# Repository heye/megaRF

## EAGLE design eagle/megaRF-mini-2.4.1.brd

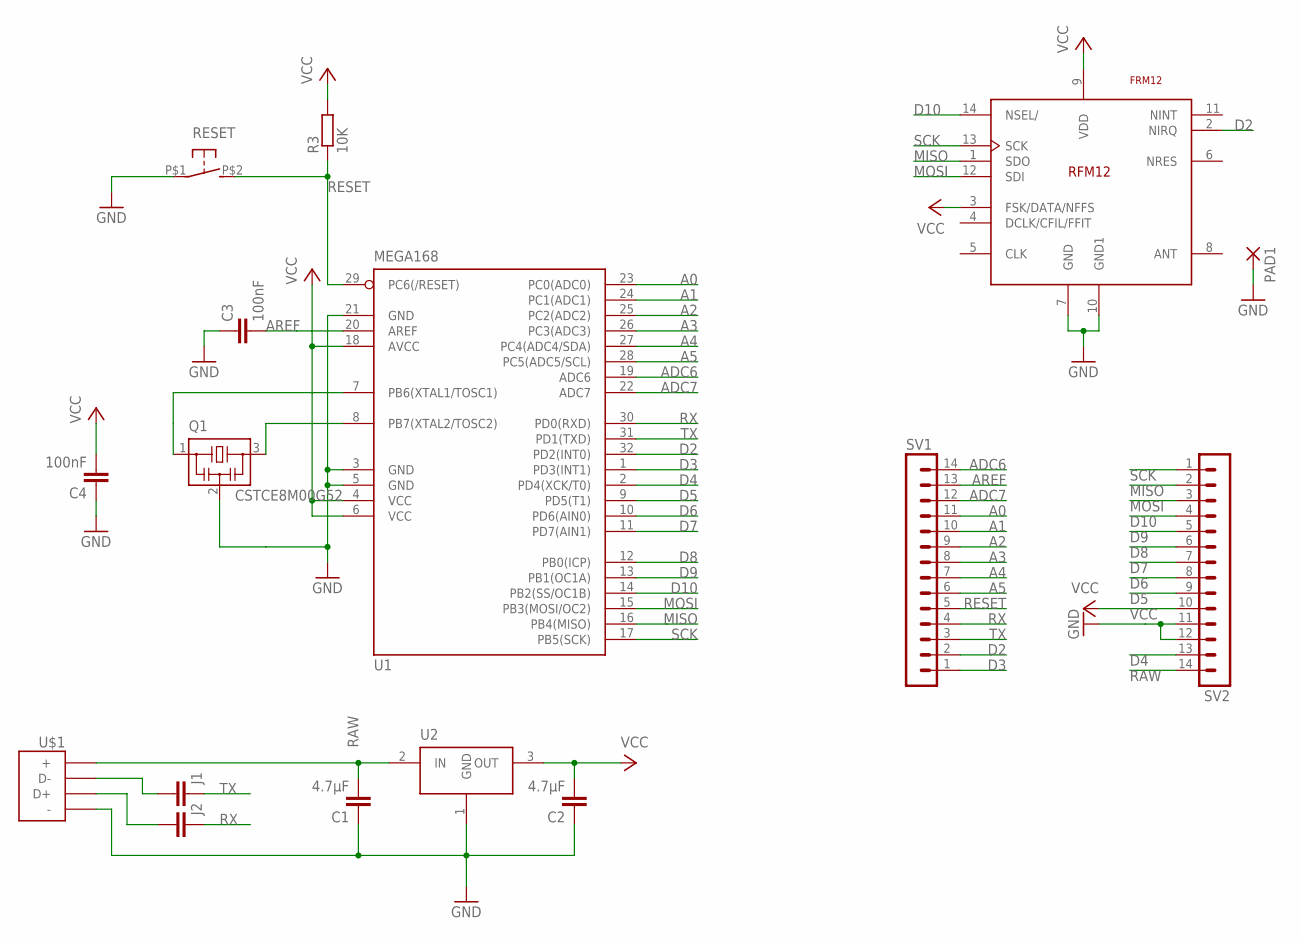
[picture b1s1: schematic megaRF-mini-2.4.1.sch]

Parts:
C1, C2: 4.7µF; C0805
C3, C4: 100nF; C0603K
J1, J2: C-EUC0402; C0402
PAD1: SMD2; SMD1,27-2,54
Q1: CSTCE8M00G52
R3: 10K; R0603
RESET: DTSM-3; DTSM31N
RFM12: FRM12; RFM12
SV1, SV2: MA14-1
U1: MEGA168; TQFP32-08
U2: TS1117CP33; TO252
U$1: USB-MICRO-B-RS

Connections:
A0: SV1.11, U1.23 (PC0(ADC0))
A1: SV1.10, U1.24 (PC1(ADC1))
A2: SV1.9, U1.25 (PC2(ADC2))
A3: SV1.8, U1.26 (PC3(ADC3))
A4: SV1.7, U1.27 (PC4(ADC4/SDA))
A5: SV1.6, U1.28 (PC5(ADC5/SCL))
ADC6: SV1.14, U1.19 (ADC6)
ADC7: SV1.12, U1.22 (ADC7)
AREF: C3.2, SV1.13, U1.20 (AREF)
D2: RFM12.2 (NIRQ), SV1.2, U1.32 (PD2(INT0))
D3: SV1.1, U1.1 (PD3(INT1))
D4: SV2.13, U1.2 (PD4(XCK/T0))
D5: SV2.9, U1.9 (PD5(T1))
D6: SV2.8, U1.10 (PD6(AIN0))
D7: SV2.7, U1.11 (PD7(AIN1))
D8: SV2.6, U1.12 (PB0(ICP))
D9: SV2.5, U1.13 (PB1(OC1A))
D10: RFM12.14 (NSEL/), SV2.4, U1.14 (PB2(SS/OC1B))
GND: C1.1, C2.1, C3.1, C4.1, PAD1.1, Q1.2, RESET.P$1, RFM12.7 (GND), RFM12.10 (GND1), SV2.11, SV2.12, U1.3 (GND), U1.5 (GND), U1.21 (GND), U2.1 (GND), U$1.P$5 (-)
MISO: RFM12.1 (SDO), SV2.2, U1.16 (PB4(MISO))
MOSI: RFM12.12 (SDI), SV2.3, U1.15 (PB3(MOSI/OC2))
unnamed: J2.1, U$1.P$3 (D+)
unnamed: J1.2, U$1.P$2 (D-)
unnamed: Q1.1, U1.7 (PB6(XTAL1/TOSC1))
unnamed: Q1.3, U1.8 (PB7(XTAL2/TOSC2))
RAW: C1.2, SV2.14, U2.2 (IN), U$1.P$1 (+)
RESET: R3.1, RESET.P$2 (S), SV1.5, U1.29 (PC6(/RESET))
RX: J2.2, SV1.4, U1.30 (PD0(RXD))
SCK: RFM12.13 (SCK), SV2.1, U1.17 (PB5(SCK))
TX: J1.1, SV1.3, U1.31 (PD1(TXD))
VCC: C2.2, C4.2, R3.2, RFM12.3 (FSK/DATA/NFFS), RFM12.9 (VDD), SV2.10, U1.4 (VCC), U1.6 (VCC), U1.18 (AVCC), U2.3 (OUT)

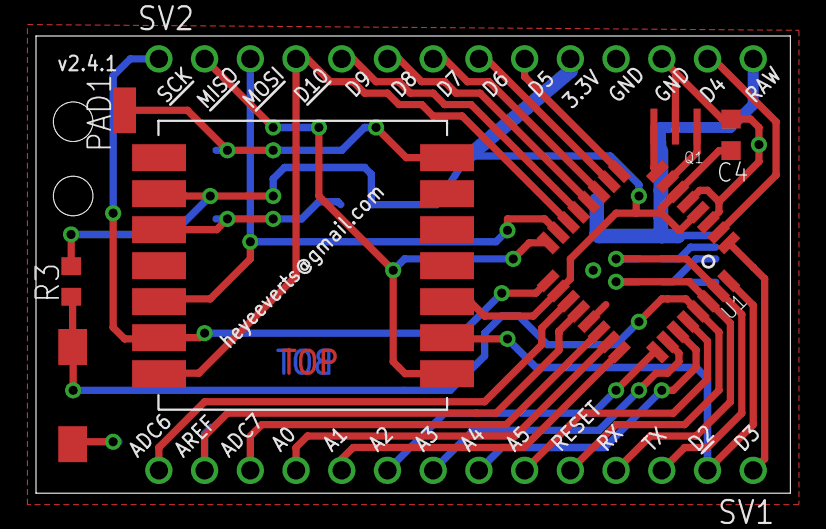
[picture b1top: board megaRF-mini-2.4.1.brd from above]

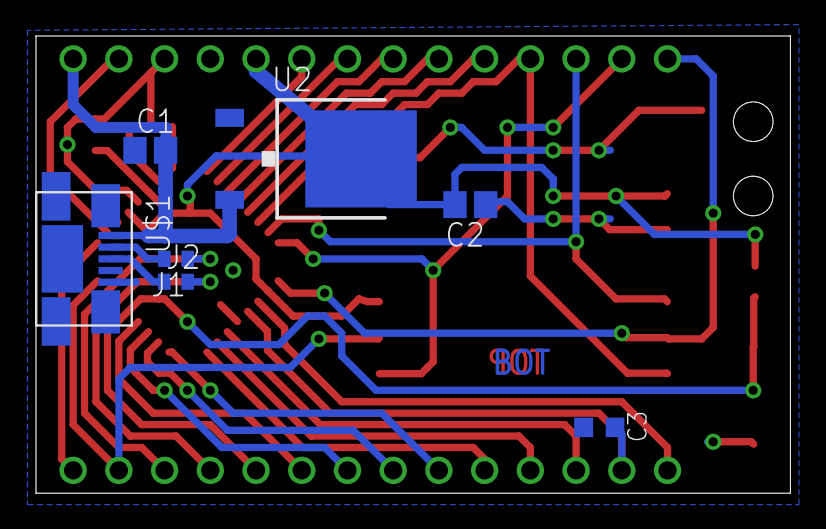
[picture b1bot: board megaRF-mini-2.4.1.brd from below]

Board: 2 copper layers, 41.9 x 25.4 mm, 16 parts (7 on the bottom side), 31 nets.
